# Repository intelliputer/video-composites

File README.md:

## Video Composites

Hardware designs and reference material for adding baseband composite-video
and mono-audio outputs to vintage consoles. The repository preserves separate
Atari 2600 and Intellivision amplifier designs while developing a better
documented universal direction for consoles that expose composite video ahead
of their RF modulator.

> These are baseband-video modifications, not RF-to-composite converters. A
> console must provide a suitable pre-RF video signal, regulated +5 V, ground,
> and, where used, raw mono audio.

### Current state

| Design | Purpose | State |
| --- | --- | --- |
| [Atari 2600](atari/README.md) | Adjustable two-stage composite-video amplifier and mono-audio pass-through. | Source design preserved; resolve or explicitly waive the recorded PCB DRC items before manufacturing. |
| [Intellivision](intellivision/doc/COMPATIBILITY.md) | Fixed-gain two-stage composite-video amplifier and mono-audio coupling for NTSC Intellivision-family consoles. | Source schematic and PCB now have zero parity issues and zero ERC errors; review/waive recorded legacy warnings and complete first-article, 75-ohm-load validation before manufacture. |
| [Universal](universal/README.md) | Proposed adjustable, AC-coupled two-stage design for appropriate baseband sources. | Design direction and prototype documentation; validate on target hardware before release or production. |

Validation details and reproducible KiCad checks are in [reports/README.md](reports/README.md).

### Atari 2600 composite amplifier

The Atari board uses a 2N3904 input stage, a 2N3906 output stage, and an
adjustable gain trimmer. It takes regulated +5 V, ground, raw pre-RF video,
and raw audio from the specific console revision, then provides buffered video
and mono audio for external RCA connectors.

Start with the [Atari design and installation notes](atari/README.md) and its
[BOM](atari/doc/BOM.md). Board revisions, video taps, and physical mounting
vary; confirm the signals on the actual console rather than copying solder
points from another revision.

### Intellivision composite amplifier

The Intellivision board uses two 2N3904 stages with AC coupling and fixed
component values. It is intended for NTSC Intellivision I, Intellivision II,
and Sears Telegames / Super Video Arcade 497.75022 consoles, subject to the
[compatibility and installation notes](intellivision/doc/COMPATIBILITY.md).

The repository includes board imagery, a reconstructed circuit analysis, and
the [BOM](intellivision/doc/BOM.md). The populated KiCad PCB has a matching
source schematic with zero current parity issues and zero ERC errors. It remains a
pre-production candidate: disposition the recorded legacy warnings and validate
an assembled board into a 75-ohm composite load before placing a manufacture
order.

#### Production Gerber reference

[`intellivision/gerbers/archive/ec.zip`](intellivision/gerbers/archive/ec.zip) is the
preserved successful EC/manufacturer-compatible Gerber package, renamed from
`old.zip`. It is the known-good reference for the post-export, pre-submission
packaging check: compare a newly exported intended submission against its
required layers, drill data, files, and naming before ordering. Its provenance
does not make it an Atari board or prove that an altered board is ready to
manufacture. See the [Gerber-package note](intellivision/gerbers/README.md).

### Universal direction

The [universal design note](universal/README.md) compares the two existing
amplifiers and proposes an adjustable-gain, AC-coupled design with explicit
supply decoupling. It is intended as a future common platform, not evidence
that either existing board is electrically interchangeable with the other.

### Before modifying a console or ordering boards

1. Verify that the target console exposes baseband composite video before its RF modulator.
2. Confirm raw video, audio, +5 V, and ground on the individual motherboard.
3. Use short shielded video wiring and test with a properly terminated 75-ohm composite input.
4. Check polarity, signal level, sync, colour, black level, and bright-scene clipping before permanent installation.
5. Review the relevant validation report and, for Gerber submissions, complete the applicable manufacturer packaging check.

### Repository layout

```text
atari/          Atari 2600 source, BOM, analysis, and installation references
intellivision/  Intellivision source, documents, and production Gerber references
universal/      Common-design proposal, prototype material, and KiCad work
reports/        Recorded ERC/DRC status and commands for reproducing checks
```

### License

This project is licensed under the [GNU General Public License v3.0](LICENSE).

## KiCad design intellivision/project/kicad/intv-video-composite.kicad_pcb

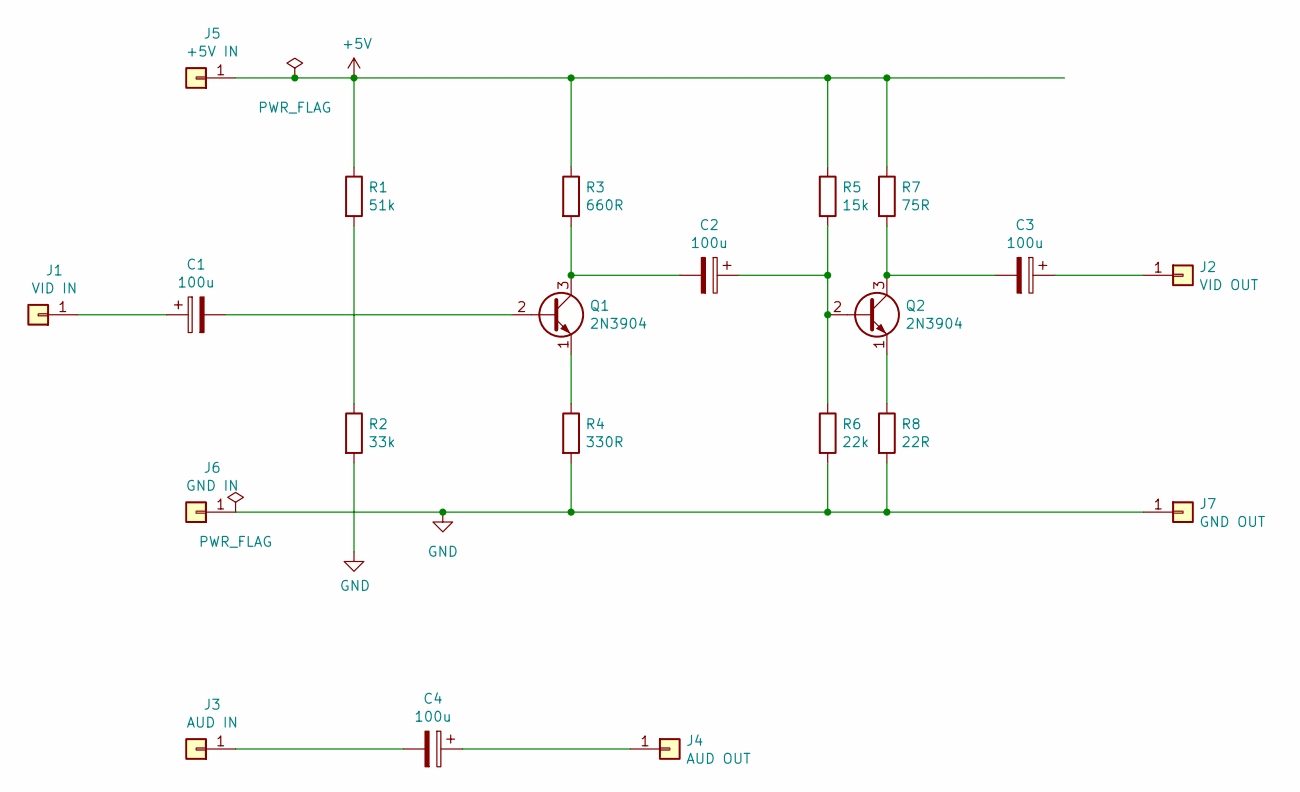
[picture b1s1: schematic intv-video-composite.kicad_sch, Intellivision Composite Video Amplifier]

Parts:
C1, C2, C3, C4: 100u; CP_Radial_D6.3mm_P2.50mm
J1: VID IN; WirePad_1x01_D3.5mm_Drill1.3mm
J2: VID OUT; WirePad_1x01_D3.5mm_Drill1.3mm
J3: AUD IN; WirePad_1x01_D3.5mm_Drill1.3mm
J4: AUD OUT; WirePad_1x01_D3.5mm_Drill1.3mm
J5: +5V IN; WirePad_1x01_D3.5mm_Drill1.3mm
J6: GND IN; WirePad_1x01_D3.5mm_Drill1.3mm
J7: GND OUT; WirePad_1x01_D3.5mm_Drill1.3mm
Q1, Q2: 2N3904; TO-92_Inline_OAR175
R1: 51k; R_Axial_DIN0207_L6.3mm_D2.5mm_P10.16mm_Horizontal
R2: 33k; R_Axial_DIN0207_L6.3mm_D2.5mm_P10.16mm_Horizontal
R3: 660R; R_Axial_DIN0207_L6.3mm_D2.5mm_P10.16mm_Horizontal
R4: 330R; R_Axial_DIN0207_L6.3mm_D2.5mm_P10.16mm_Horizontal
R5: 15k; R_Axial_DIN0207_L6.3mm_D2.5mm_P10.16mm_Horizontal
R6: 22k; R_Axial_DIN0207_L6.3mm_D2.5mm_P10.16mm_Horizontal
R7: 75R; R_Axial_DIN0207_L6.3mm_D2.5mm_P10.16mm_Horizontal
R8: 22R; R_Axial_DIN0207_L6.3mm_D2.5mm_P10.16mm_Horizontal

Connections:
+5V: J5.1 (Pin_1_1), R1.1, R3.1, R5.1, R7.1
GND: J6.1 (Pin_1_1), J7.1 (Pin_1_1), R2.2, R4.2, R6.2, R8.2
unnamed: C1.1, J1.1 (Pin_1_1)
unnamed: C3.1, J2.1 (Pin_1_1)
unnamed: C4.2, J3.1 (Pin_1_1)
unnamed: C4.1, J4.1 (Pin_1_1)
unnamed: C1.2, Q1.2 (B)
unnamed: C2.2, Q1.3 (C), R3.2
unnamed: Q1.1 (E), R4.1
unnamed: C2.1, Q2.2 (B), R5.2, R6.1
unnamed: C3.2, Q2.3 (C), R7.2
unnamed: Q2.1 (E), R8.1
unnamed: R1.2, R2.1

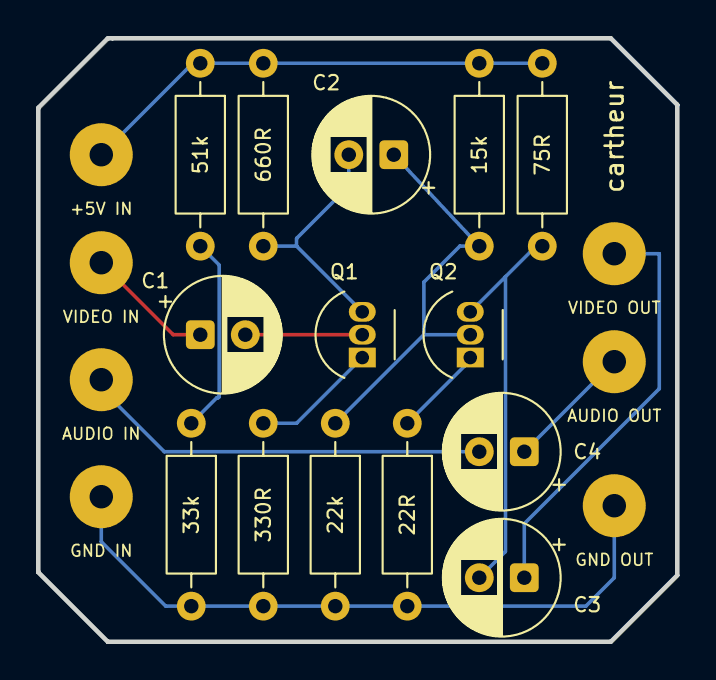
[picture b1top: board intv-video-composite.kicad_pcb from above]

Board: 2 copper layers, 35.5 x 33.5 mm, 21 parts (1 on the bottom side), 13 nets.

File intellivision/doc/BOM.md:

# Intellivision composite-video amplifier BOM

This BOM covers the reconstructed circuit shown in
[`doc/schematic.jpg`](doc/schematic.jpg) and the corresponding PCB. RCA jacks,
wire, and mounting hardware are installation-specific and are not included.

| Reference | Value / part | Qty. |
| --- | --- | ---: |
| C1, C2, C3, C4 | 100 µF electrolytic capacitor | 4 |
| R1 | 51 kΩ resistor | 1 |
| R2 | 33 kΩ resistor | 1 |
| R3 | 660 Ω resistor | 1 |
| R4 | 330 Ω resistor | 1 |
| R5 | 15 kΩ resistor | 1 |
| R6 | 22 kΩ resistor | 1 |
| R7 | 75 Ω resistor | 1 |
| R8 | 22 Ω resistor | 1 |
| Q1, Q2 | 2N3904 NPN transistor, TO-92 | 2 |

Observe the polarity of C1–C4. For installation, also provide yellow video
and mono-audio RCA jacks, 75 Ω coax or short shielded cable for raw video, and
hookup wire for audio, regulated +5 V, and ground.

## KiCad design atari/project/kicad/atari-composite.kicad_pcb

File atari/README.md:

## Atari 2600 composite-video amplifier

This is the selected quality-focused composite-video modification for an Atari
2600. It taps the console's pre-RF video and audio signals, buffers the video,
and provides composite video plus mono audio for RCA connectors. It is not an
RF-to-composite demodulator.

The board implements a two-stage discrete transistor amplifier based on a
design by `simon.plata`. Compared with the single-transistor alternative that
was evaluated for this repository, this circuit provides adjustable video gain
and is the preferred option where the best composite-video result is more
important than the lowest component count.

> Composite output is still composite output: it is a substantial improvement
> over RF, but it cannot equal an RGB or S-Video modification.

## Project files

| What | Location |
| --- | --- |
| KiCad schematic | [`project/kicad/atari-composite.kicad_sch`](project/kicad/atari-composite.kicad_sch) |
| KiCad PCB layout | [`project/kicad/atari-composite.kicad_pcb`](project/kicad/atari-composite.kicad_pcb) |
| KiCad project | [`project/kicad/atari-composite.kicad_pro`](project/kicad/atari-composite.kicad_pro) |
| Installation/result photographs | [`gallery/`](gallery/) |
| Rendered PCB snapshot | [`doc/pcb-snapshot.png`](doc/pcb-snapshot.png) |
| Bill of materials | [`doc/BOM.md`](doc/BOM.md) |
| Circuit analysis | [`doc/CIRCUIT-ANALYSIS.md`](doc/CIRCUIT-ANALYSIS.md) |

## Circuit summary

The video path uses a 2N3904 first stage and a 2N3906 output stage. `RV1`
adjusts video gain/brightness, allowing the output level to be set for the
particular console and display chain. Audio is routed separately to the audio
output.

Component count for the amplifier is 12:

- 2 transistors;
- 8 fixed resistors;
- 1 trimmer potentiometer; and
- 1 capacitor.

## Bill of materials

| Reference | Value / part | Qty. |
| --- | --- | ---: |
| C1 | 47 pF ceramic capacitor | 1 |
| R1, R3 | 1 kΩ resistor | 2 |
| R2 | 3.3 kΩ resistor | 1 |
| R4 | 150 Ω resistor | 1 |
| R5 | 68 Ω resistor | 1 |
| R6 | 18 Ω resistor | 1 |
| R7 | 75 Ω resistor | 1 |
| R8 | 10 kΩ resistor | 1 |
| RV1 | 5 kΩ 3296W trimmer potentiometer | 1 |
| Q1 | 2N3904, TO-92 | 1 |
| Q2 | 2N3906, TO-92 | 1 |

Use 1% resistors and a short, shielded video-input lead where practical.

## Installation notes

This board requires four console-side connections: regulated +5 V, ground,
raw video before the RF modulator, and raw audio. Connect the buffered video
and audio outputs to the centre contacts of their RCA jacks; connect the RCA
shells to ground.

Atari 2600 motherboard revisions, NTSC/PAL variants, and case styles have
different RF sections and convenient connection points. Inspect the specific
board and verify each signal with its schematic before soldering. Do not copy
connection points from a different revision without checking them. Disconnect
power before opening the console, and adjust `RV1` only after confirming a
stable picture on the intended display or scaler.

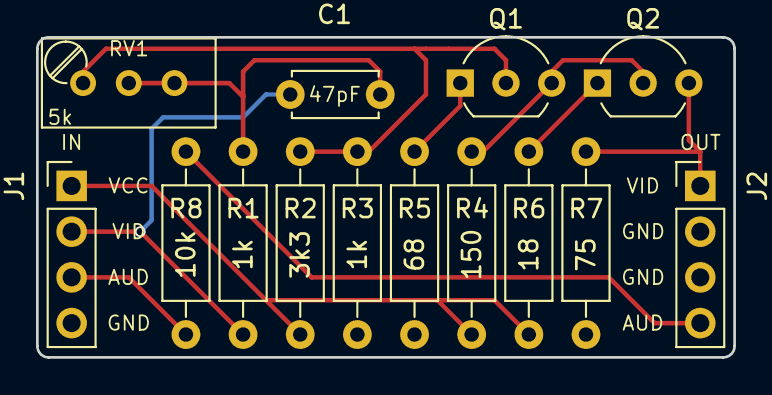
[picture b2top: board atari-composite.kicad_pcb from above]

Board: 2 copper layers, 38.7 x 17.8 mm, 14 parts (0 on the bottom side), 11 nets.

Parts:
C1: 47pF; C_Disc_D4.7mm_W2.5mm_P5.00mm
J1: Video; Pin_Header_Straight_1x04_Pitch2.54mm
J2: Output; Pin_Header_Straight_1x04_Pitch2.54mm
Q1: 2N3904; TO-92_Inline_Wide
Q2: 2N3906; TO-92_Inline_Wide
R1, R3: 1k; R_Axial_DIN0207_L6.3mm_D2.5mm_P10.16mm_Horizontal
R2: 3k3; R_Axial_DIN0207_L6.3mm_D2.5mm_P10.16mm_Horizontal
R4: 150; R_Axial_DIN0207_L6.3mm_D2.5mm_P10.16mm_Horizontal
R5: 68; R_Axial_DIN0207_L6.3mm_D2.5mm_P10.16mm_Horizontal
R6: 18; R_Axial_DIN0207_L6.3mm_D2.5mm_P10.16mm_Horizontal
R7: 75; R_Axial_DIN0207_L6.3mm_D2.5mm_P10.16mm_Horizontal
R8: 10k; R_Axial_DIN0207_L6.3mm_D2.5mm_P10.16mm_Horizontal
RV1: 5k; Potentiometer_Trimmer_Bourns_3296W

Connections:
/AUD_IN: J1.3, R8.1
/AUD_OUT: J2.4, R8.2
/VID_IN: C1.2, J1.2, R1.1
/VID_OUT: J2.1, Q2.3, R7.2
GND: J1.4, J2.2, J2.3, R3.1, R5.1, R7.1
unnamed: C1.1, R1.2, RV1.2, RV1.3
unnamed: Q1.1, R5.2
unnamed: Q1.2, R2.2, R3.2, RV1.1
unnamed: Q1.3, Q2.2, R4.2
unnamed: Q2.1, R6.2
VCC: J1.1, R2.1, R4.1, R6.1

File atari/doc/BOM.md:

# Atari 2600 composite-video amplifier BOM

This BOM covers the components fitted to the PCB in
[`project/kicad/`](project/kicad/). Panel connectors, wire, and mounting
hardware are installation-specific and are not included.

| Reference | Value / part | Qty. |
| --- | --- | ---: |
| C1 | 47 pF ceramic capacitor | 1 |
| R1, R3 | 1 kΩ resistor | 2 |
| R2 | 3.3 kΩ resistor | 1 |
| R4 | 150 Ω resistor | 1 |
| R5 | 68 Ω resistor | 1 |
| R6 | 18 Ω resistor | 1 |
| R7 | 75 Ω resistor | 1 |
| R8 | 10 kΩ resistor | 1 |
| RV1 | 5 kΩ 3296W trimmer potentiometer | 1 |
| Q1 | 2N3904, TO-92 | 1 |
| Q2 | 2N3906, TO-92 | 1 |

For the installation, also provide RCA jacks or a composite A/V cable,
shielded wire for video, hookup wire for audio/power/ground, and a suitable
mounting method.

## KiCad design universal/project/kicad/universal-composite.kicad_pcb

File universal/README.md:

# Universal baseband composite-video amplifier: comparison and recommendation

This note compares the Atari 2600 and Intellivision amplifier approaches in
this repository and proposes a common design direction for consoles that make
**baseband composite video available before their RF modulator**.

It is intended for NTSC Intellivision I, Intellivision II, and Sears Telegames
/ Super Video Arcade 497.75022, as well as an Atari 2600 after the correct
pre-RF video tap has been identified. It is not an RF-to-composite converter,
and it cannot make an RF-only or RGB-only signal compatible without an
appropriate preceding circuit.

## Behavioural comparison

| Behaviour | Atari board | Intellivision board |
| --- | --- | --- |
| Gain setup | Adjustable with `RV1`; the installer can set composite amplitude/brightness for the particular console and display. | Fixed by the resistor values; predictable once built, but not adjustable. |
| Active stages | NPN first stage followed by PNP second stage. | Two NPN common-emitter stages. |
| Video-stage coupling | Primarily DC-coupled, so the operating point of one stage affects the next. | AC-coupled by `C1`, `C2`, and `C3`; each stage can use its own DC bias. |
| Output | Tunable amplitude and good drive flexibility, but needs careful trim adjustment. | Fixed amplitude and DC-blocked output, but less able to compensate for console/display variation. |
| Low-frequency behaviour | No large electrolytic coupling capacitors in the video path. | Three 100 uF video coupling capacitors; correct polarity and capacitor condition matter to black-level stability. |
| Installation risks | Excess gain can clip bright areas or disturb sync. | Incorrect capacitor polarity or a fixed level unsuited to the display can impair the picture. |

Both designs use two inverting common-emitter stages, restoring the input
video polarity at the final output. Both expect a short shielded lead and a
75-ohm terminated composite display input.

## Recommended common circuit direction

The best general-purpose circuit is a **two-stage, non-inverting discrete
amplifier with AC-coupled interfaces and adjustable gain**:

```text
raw composite in
  -> DC-blocking input capacitor
  -> high-impedance, adjustable bias/gain network
  -> NPN common-emitter gain stage
  -> DC-blocking interstage capacitor
  -> PNP (or NPN) common-emitter output stage
  -> DC-blocking output capacitor
  -> 75-ohm series output resistor
  -> composite jack / 75-ohm display termination
```

Add a 100 nF ceramic capacitor and a 10 uF electrolytic capacitor directly
between +5 V and ground at the board. Neither existing design shows dedicated
local supply decoupling; it is inexpensive insurance against supply noise and
oscillation.

### Why this hybrid is preferred

- It retains the Atari circuit's adjustable gain, which is valuable because
  source level, cable loss, and display/scaler input tolerance vary.
- It retains the Intellivision circuit's AC isolation. The source, first
  stage, second stage, and external display can each keep an appropriate DC
  operating point rather than depending on one another.
- Two common-emitter stages retain video polarity while providing voltage gain
  and sufficient output current.
- A 75-ohm series output resistor makes the board behave as a conventional
  composite source when feeding a properly terminated cable/display.
- Input coupling prevents an unknown console-side DC offset from shifting the
  amplifier bias. Output coupling ensures no amplifier DC reaches the RCA
  connector.

## Recommended implementation details

Use the Atari topology as the starting point because its trim control is the
most useful practical feature, but revise it as follows:

1. Add an input coupling capacitor ahead of the gain-control/bias node.
   Choose a low-leakage capacitor and calculate its value together with the
   input impedance so the lower cutoff is far below video content; do not
   copy the Intellivision's 100 uF value blindly.
2. AC-couple the stages so their DC biases can be set independently, as in the
   Intellivision design.
3. Add an output coupling capacitor if the final transistor collector carries
   DC, then place the 75-ohm series resistor at the RCA/output connector.
4. Include local +5 V decoupling: 100 nF ceramic in parallel with about
   10 uF electrolytic, physically close to the transistors.
5. Provide an accessible, single-turn or multiturn gain trimmer with a marked
   safe adjustment range. Set it on the target display for stable sync,
   correct black level, and no highlight clipping.
6. Use a high-impedance input and short shielded video wiring. Connect cable
   shield/RCA shell to the same low-impedance ground return as the board.

## Compatibility and limits

The **same universal board circuit** can serve NTSC Intellivision I,
Intellivision II, and Sears Telegames 497.75022 because their relevant signal
is the same raw composite video ahead of the RF modulator. The installation is
not universal: solder points, shielding, available space, power routing, and
RCA mounting vary by motherboard and chassis. See
[`../intellivision/doc/COMPATIBILITY.md`](../intellivision/doc/COMPATIBILITY.md).

No analogue board can guarantee correct results in every situation without
validation. Before committing a PCB revision, measure the actual raw-video
amplitude and DC offset for each target family, test with a 75-ohm terminated
display/scaler, and verify sync, colour, black level, and bright-scene
clipping. PAL consoles, non-standard board revisions, long unshielded leads,
and displays without 75-ohm termination require separate validation.

## Bottom line

For the listed NTSC systems, the recommended universal design is **the Atari
two-stage adjustable-gain approach improved with the Intellivision-style AC
coupling and explicit supply decoupling**. It offers the broadest margin for
source and display variation while preserving the correct composite waveform.

## Prototype schematic

[`SCHEMATIC-DESIGN.md`](SCHEMATIC-DESIGN.md) contains the first-pass
2N2222A-only schematic design, using the stocked Diotec TO-92 E–B–C part,
starting values, expected DC operating points, and the required
bench-validation plan. It precedes PCB layout intentionally.

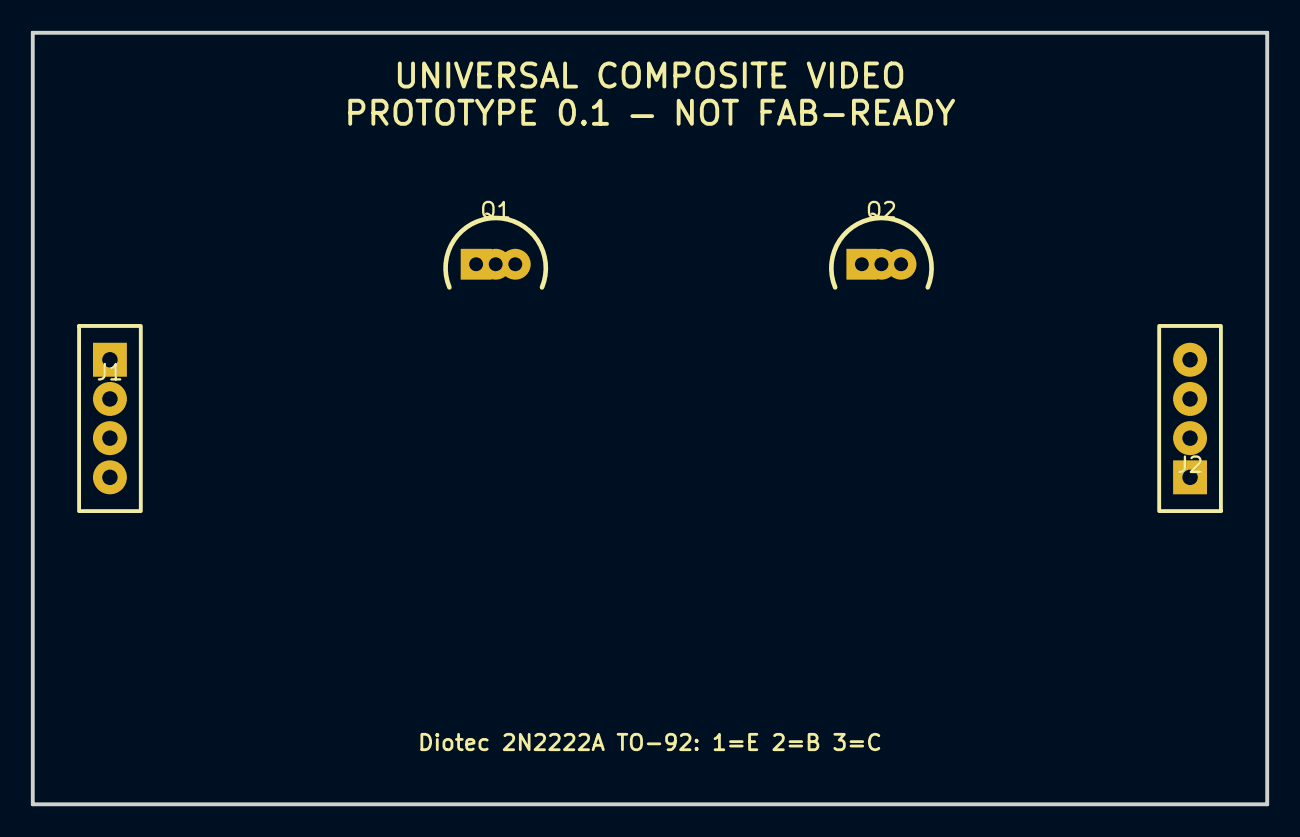
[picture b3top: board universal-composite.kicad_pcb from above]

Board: 2 copper layers, 80.0 x 50.0 mm, 4 parts (0 on the bottom side), 2 nets, no tracks yet.

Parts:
J1: CONSOLE; Header_1x04
J2: A/V OUT; Header_1x04
Q1, Q2: 2N2222A EBC; TO-92_EBC

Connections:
+5V: J1.1, J2.1
GND: J1.2, J2.2
